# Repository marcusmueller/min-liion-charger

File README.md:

# Minimal LiIon Charger

Based on the TI [bq21040](https://www.ti.com/product/BQ21040).

Thrown together in 15 min. No warranties.

It's about 18.1 mm × 15.0 mm. 

## License

(C) 2023 Marcus Müller

[CERN OHL-S v2](https://ohwr.org/cern_ohl_s_v2.txt)

## PCB 3D Render

## Schematic

## BOM

| Ref | Qnty | Value | Cmp name | Footprint | Description | Vendor | DNP |
| --- | --- | --- | --- | --- | --- | --- | --- |
| C1, C2 | 2 | 1uF | C | Capacitor_SMD:C_0805_2012Metric | Unpolarized capacitor |  |  |
| D1 | 1 | LED | LED | LED_SMD:LED_0805_2012Metric | Light emitting diode |  |  |
| J1 | 1 | Conn_01x02 | Conn_01x02 | Connector_PinSocket_2.54mm:PinSocket_2x01_P2.54mm_Vertical | Generic connector, single row, 01x02, script generated (kicad-library-utils/schlib/autogen/connector/) |  |  |
| J2 | 1 | Conn_01x03 | Conn_01x03 | Connector_PinSocket_2.54mm:PinSocket_1x03_P2.54mm_Vertical | Generic connector, single row, 01x03, script generated (kicad-library-utils/schlib/autogen/connector/) |  |  |
| R1 | 1 | 1k | R | Resistor_SMD:R_0805_2012Metric | Resistor |  |  |
| R2 | 1 | 1.5k | R | Resistor_SMD:R_0805_2012Metric | Resistor |  |  |
| U1 | 1 | bq21040 | bq21040 | Package_TO_SOT_SMD:SOT-23-6 | Voltage and Current Protection for Single-Cell Li-Ion and Li-Polymer Batteries |  |  |

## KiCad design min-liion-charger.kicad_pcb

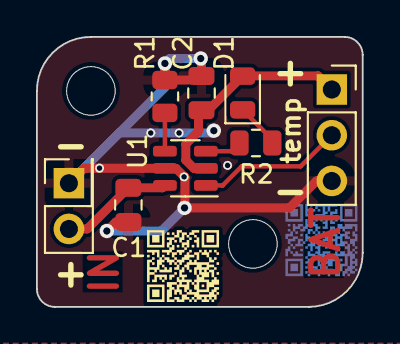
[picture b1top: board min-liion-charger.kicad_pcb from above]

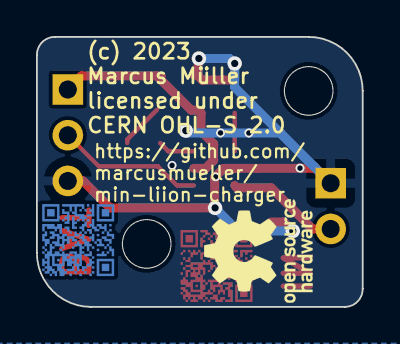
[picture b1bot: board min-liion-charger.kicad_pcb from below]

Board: 2 copper layers, 18.1 x 15.0 mm, 14 parts (2 on the bottom side), 7 nets.

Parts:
C1, C2: 1uF; C_0805_2012Metric
D1: LED; LED_0805_2012Metric
H1, H2: MountingHole; MountingHole_2.7mm_M2.5
J1: Conn_01x02; PinSocket_2x01_P2.54mm_Vertical
J2: Conn_01x03; PinSocket_1x03_P2.54mm_Vertical
R1: 1k; R_0805_2012Metric
R2: 1.5k; R_0805_2012Metric
U1: bq21040; SOT-23-6
oshwlogo1: Logo_Open_Hardware_Small; OSHW-Logo_5.7x6mm_SilkScreen
qrcode1: SYM_Arrow_Small; QR code
qrcode-copper-bottom1: SYM_Arrow_Small; qr-copper
qrcode-copper-top1: SYM_Arrow_Small; qr-copper

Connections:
/Bat+: C2.1, D1.2 (A), J2.1, U1.2 (Vout)
/Temp_sensor: J2.2, U1.1 (Temp)
GND: C1.2, C2.2, J1.1, J2.3, R1.1, U1.5 (GND)
unnamed: D1.1 (K), R2.2
unnamed: R1.2, U1.4 (Iset)
unnamed: R2.1, U1.3 (~Chg)
VCC: C1.1, J1.2, U1.6 (Vin)

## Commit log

2023-11-04 as usual, start with gitignore
2023-11-04 quickndirty
2023-11-04 shrink, better silkscreen
2023-11-04 fix dimensions
2023-11-04 slightly increase Y-size to slip into cheaper panelize-by-jlcpcb regime

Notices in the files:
min-liion-charger.kicad_pcb:
licensed under
CERN OHL-S 2.0
